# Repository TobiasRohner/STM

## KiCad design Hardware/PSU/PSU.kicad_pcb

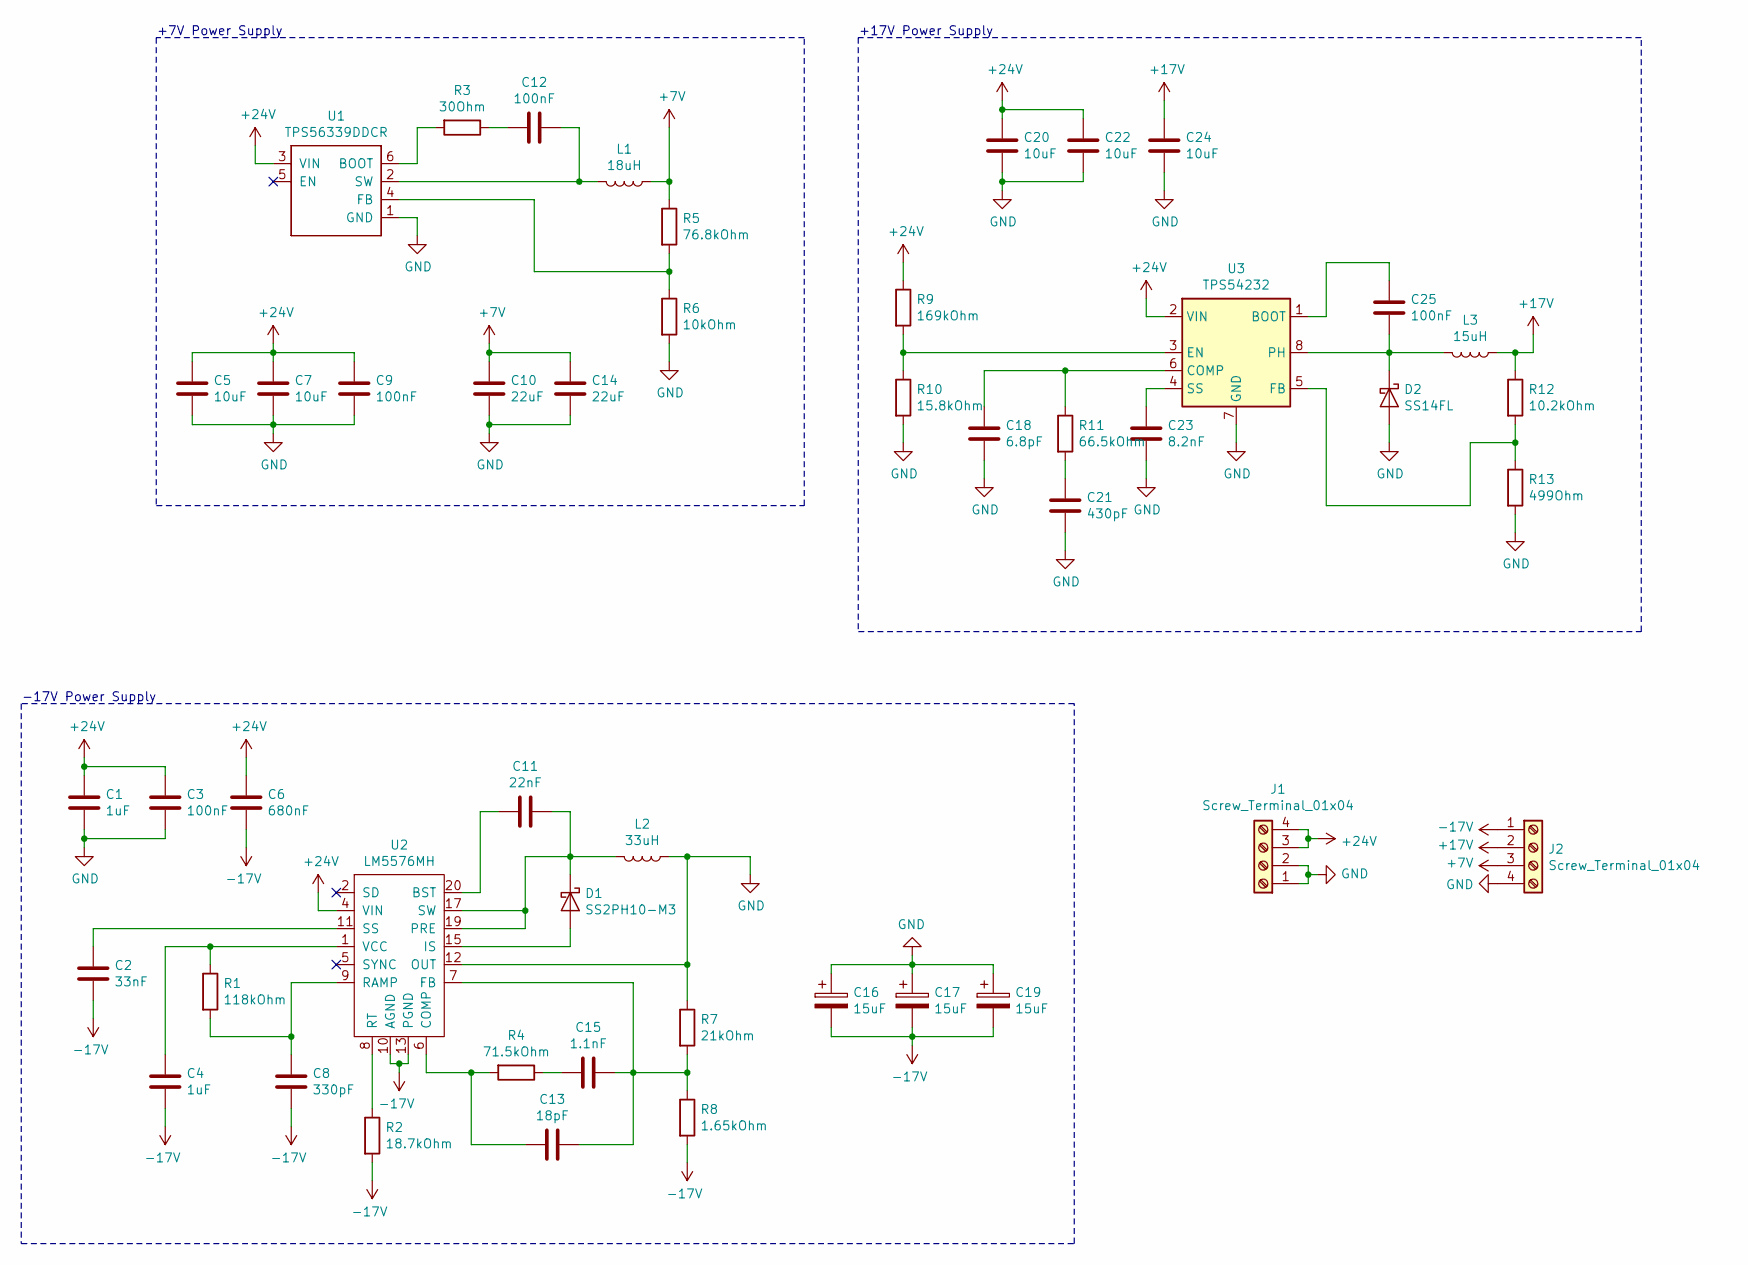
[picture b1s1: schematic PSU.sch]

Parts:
C1, C4: 1uF; C_0603_1608Metric_Pad1.05x0.95mm_HandSolder
C2: 33nF; C_0603_1608Metric_Pad1.05x0.95mm_HandSolder
C3, C9, C12: 100nF; C_0805_2012Metric_Pad1.15x1.40mm_HandSolder
C5, C7: 10uF; C_0805_2012Metric_Pad1.15x1.40mm_HandSolder
C6: 680nF; C_0805_2012Metric_Pad1.15x1.40mm_HandSolder
C8: 330pF; C_0603_1608Metric_Pad1.05x0.95mm_HandSolder
C10, C14: 22uF; C_1210_3225Metric_Pad1.42x2.65mm_HandSolder
C11: 22nF; C_0603_1608Metric_Pad1.05x0.95mm_HandSolder
C13: 18pF; C_0603_1608Metric_Pad1.05x0.95mm_HandSolder
C15: 1.1nF; C_0603_1608Metric_Pad1.05x0.95mm_HandSolder
C16, C17, C19: 15uF; CP_EIA-3528-21_Kemet-B_Pad1.50x2.35mm_HandSolder
C18: 6.8pF; C_0603_1608Metric_Pad1.05x0.95mm_HandSolder
C20, C22, C24: 10uF; C_1206_3216Metric_Pad1.42x1.75mm_HandSolder
C21: 430pF; C_0603_1608Metric_Pad1.05x0.95mm_HandSolder
C23: 8.2nF; C_0201_0603Metric
C25: 100nF; C_0603_1608Metric_Pad1.05x0.95mm_HandSolder
D1: SS2PH10-M3; DO-220AA
D2: SS14FL; SMAF
J1, J2: Screw_Terminal_01x04; BarrierBlock
L1: 18uH; MWSA1206S
L2: 33uH; MWSA1206S
L3: 15uH; MSA75-150M
R1: 118kOhm; R_0603_1608Metric_Pad1.05x0.95mm_HandSolder
R2: 18.7kOhm; R_0603_1608Metric_Pad1.05x0.95mm_HandSolder
R3: 30Ohm; R_0603_1608Metric_Pad1.05x0.95mm_HandSolder
R4: 71.5kOhm; R_0603_1608Metric_Pad1.05x0.95mm_HandSolder
R5: 76.8kOhm; R_0603_1608Metric_Pad1.05x0.95mm_HandSolder
R6: 10kOhm; R_0603_1608Metric_Pad1.05x0.95mm_HandSolder
R7: 21kOhm; R_0603_1608Metric_Pad1.05x0.95mm_HandSolder
R8: 1.65kOhm; R_0603_1608Metric_Pad1.05x0.95mm_HandSolder
R9: 169kOhm; R_0603_1608Metric_Pad1.05x0.95mm_HandSolder
R10: 15.8kOhm; R_0603_1608Metric_Pad1.05x0.95mm_HandSolder
R11: 66.5kOhm; R_0603_1608Metric_Pad1.05x0.95mm_HandSolder
R12: 10.2kOhm; R_0603_1608Metric_Pad1.05x0.95mm_HandSolder
R13: 499Ohm; R_0603_1608Metric_Pad1.05x0.95mm_HandSolder
U1: TPS56339DDCR; TSOT-23-6_HandSoldering
U2: LM5576MH; HTSSOP-20-1EP_4.4x6.5mm_P0.65mm_EP3.4x6.5mm_Mask2.75x3.43mm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
U3: TPS54232; SOIC-8_3.9x4.9mm_P1.27mm

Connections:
+7V: C10.1, C14.1, J2.3, L1.1, R5.1
+17V: C24.1, J2.2, L3.1, R12.1
+24V: C1.1, C3.1, C5.1, C6.1, C7.1, C9.1, C20.1, C22.1, J1.3, J1.4, R9.1, U1.3 (VIN), U2.3 (VIN), U2.4 (VIN), U3.2 (VIN)
-17V: C2.2, C4.2, C6.2, C8.2, C16.2, C17.2, C19.2, J2.1, R2.2, R8.2, U2.10 (AGND), U2.13 (PGND), U2.14 (PGND), U2.21 (AGND)
GND: C1.2, C3.2, C5.2, C7.2, C9.2, C10.2, C14.2, C16.1, C17.1, C18.2, C19.1, C20.2, C21.2, C22.2, C23.2, C24.2, D2.2 (A), J1.1, J1.2, J2.4, L2.1, R6.2, R7.1, R10.2, R13.2, U1.1 (GND), U2.12 (OUT), U3.7 (GND)
unnamed: C2.1, U2.11 (SS)
unnamed: C4.1, R1.1, U2.1 (VCC)
unnamed: C8.1, R1.2, U2.9 (RAMP)
unnamed: C11.1, D1.1 (K), L2.2, U2.17 (SW), U2.18 (SW), U2.19 (PRE)
unnamed: C11.2, U2.20 (BST)
unnamed: C12.1, L1.2, U1.2 (SW)
unnamed: C12.2, R3.1
unnamed: C13.1, C15.1, R7.2, R8.1, U2.7 (FB)
unnamed: C13.2, R4.2, U2.6 (COMP)
unnamed: C15.2, R4.1
unnamed: C18.1, R11.1, U3.6 (COMP)
unnamed: C21.1, R11.2
unnamed: C23.1, U3.4 (SS)
unnamed: C25.1, U3.1 (BOOT)
unnamed: C25.2, D2.1 (K), L3.2, U3.8 (PH)
unnamed: D1.2 (A), U2.15 (IS), U2.16 (IS)
unnamed: R2.1, U2.8 (RT)
unnamed: R3.2, U1.6 (BOOT)
unnamed: R5.2, R6.1, U1.4 (FB)
unnamed: R9.2, R10.1, U3.3 (EN)
unnamed: R12.2, R13.1, U3.5 (FB)

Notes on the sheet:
+7V Power Supply
+17V Power Supply
-17V Power Supply

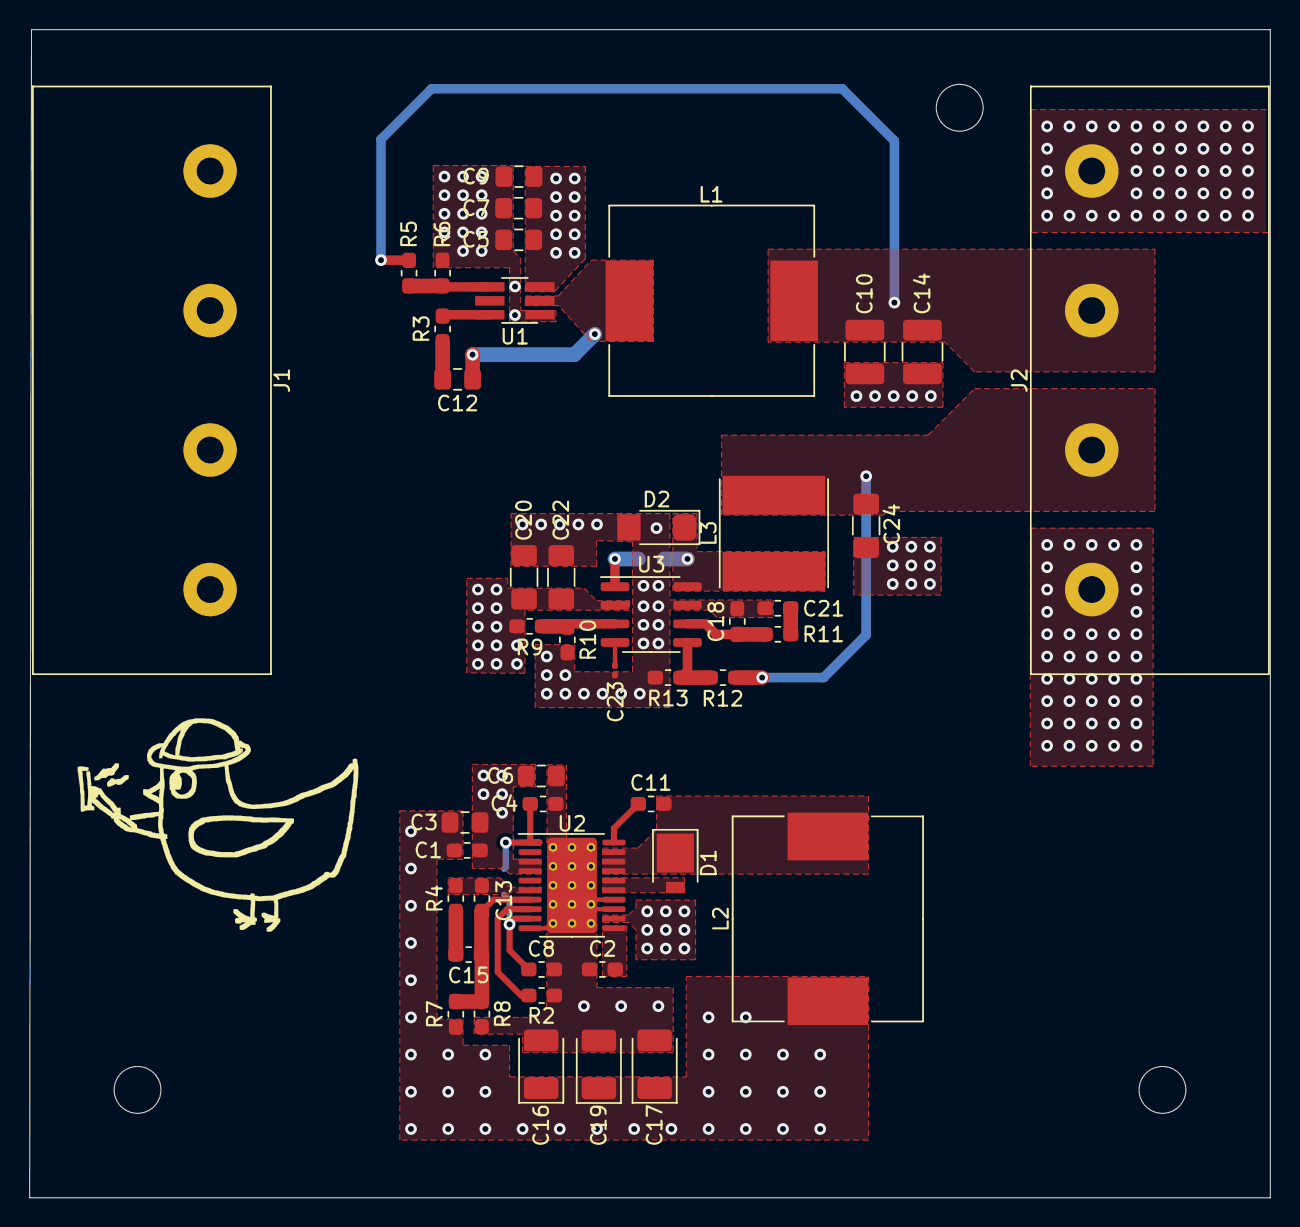
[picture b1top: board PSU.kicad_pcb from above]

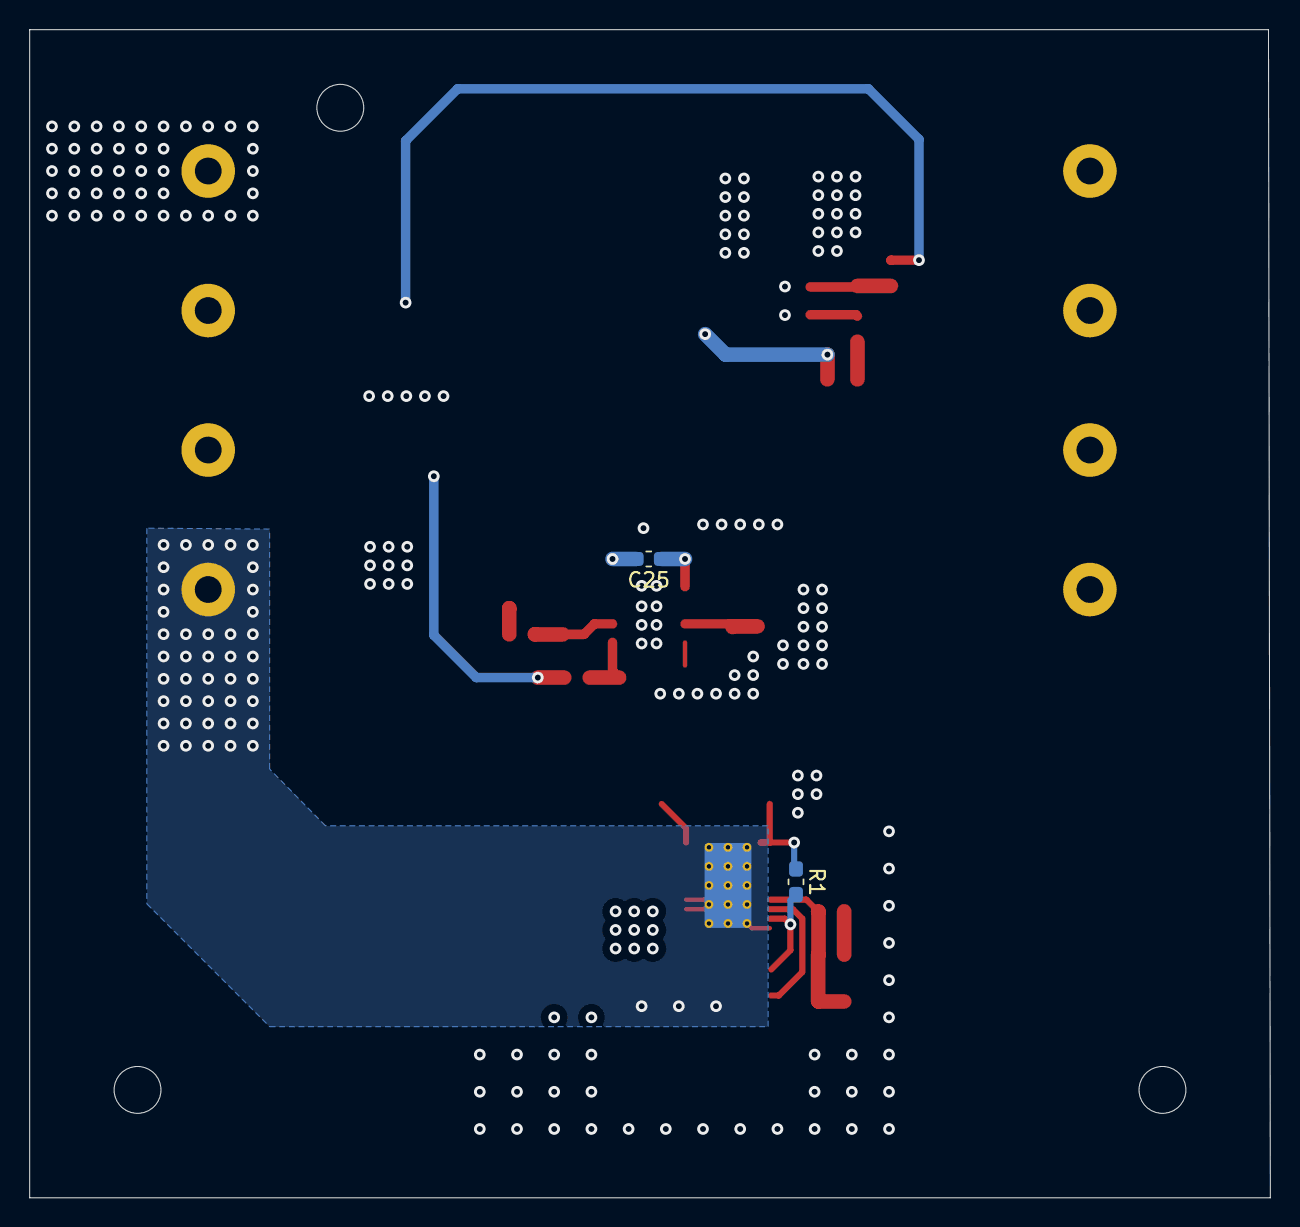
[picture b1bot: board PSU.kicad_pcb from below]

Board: 4 copper layers, 84.7 x 79.8 mm, 48 parts (2 on the bottom side), 26 nets.

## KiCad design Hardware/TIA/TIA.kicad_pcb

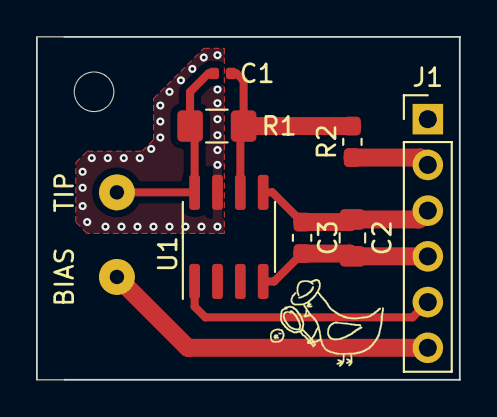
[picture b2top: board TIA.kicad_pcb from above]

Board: 2 copper layers, 23.5 x 19.1 mm, 9 parts (0 on the bottom side), 7 nets.

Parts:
C1: 300fF; C_0402_1005Metric
C2: 4.7uF; C_0805_2012Metric_Pad1.15x1.40mm_HandSolder
C3: 100nF; C_0603_1608Metric_Pad1.05x0.95mm_HandSolder
J1: Conn_01x06_Male; PinHeader_1x06_P2.54mm_Vertical
J2: TIP; SolderWirePad_1x01_Drill0.8mm
J3: BIAS; SolderWirePad_1x01_Drill0.8mm
R1: 100MOhm; R_1206_3216Metric_Pad1.42x1.75mm_HandSolder
R2: 750Ohm; R_0603_1608Metric_Pad1.05x0.95mm_HandSolder
U1: ADA4530-1; SOIC-8_3.9x4.9mm_P1.27mm

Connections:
+15V: C2.1, C3.1, J1.3, U1.5
BIAS: J1.6, J3.1
GND: C2.2, C3.2, J1.1, J1.4, U1.4
unnamed: C1.1, R1.1, R2.2, U1.6
unnamed: C1.2, J2.1, R1.2, U1.8
TIA_DATA: J1.2, R2.1
V_TIP: J1.5, U1.1

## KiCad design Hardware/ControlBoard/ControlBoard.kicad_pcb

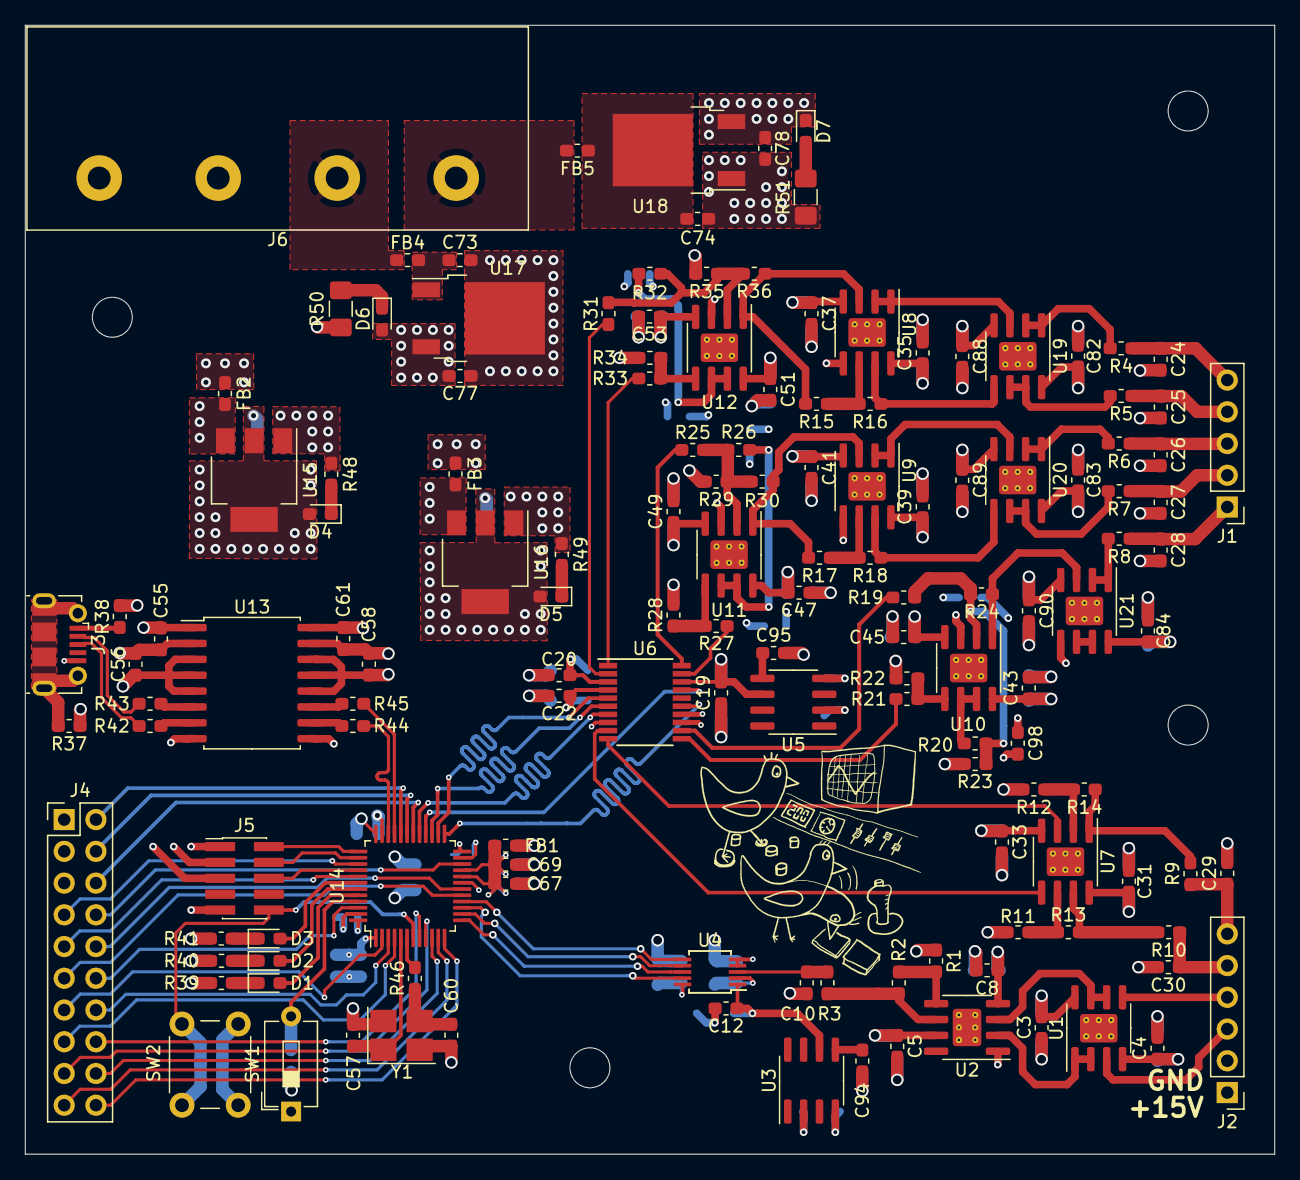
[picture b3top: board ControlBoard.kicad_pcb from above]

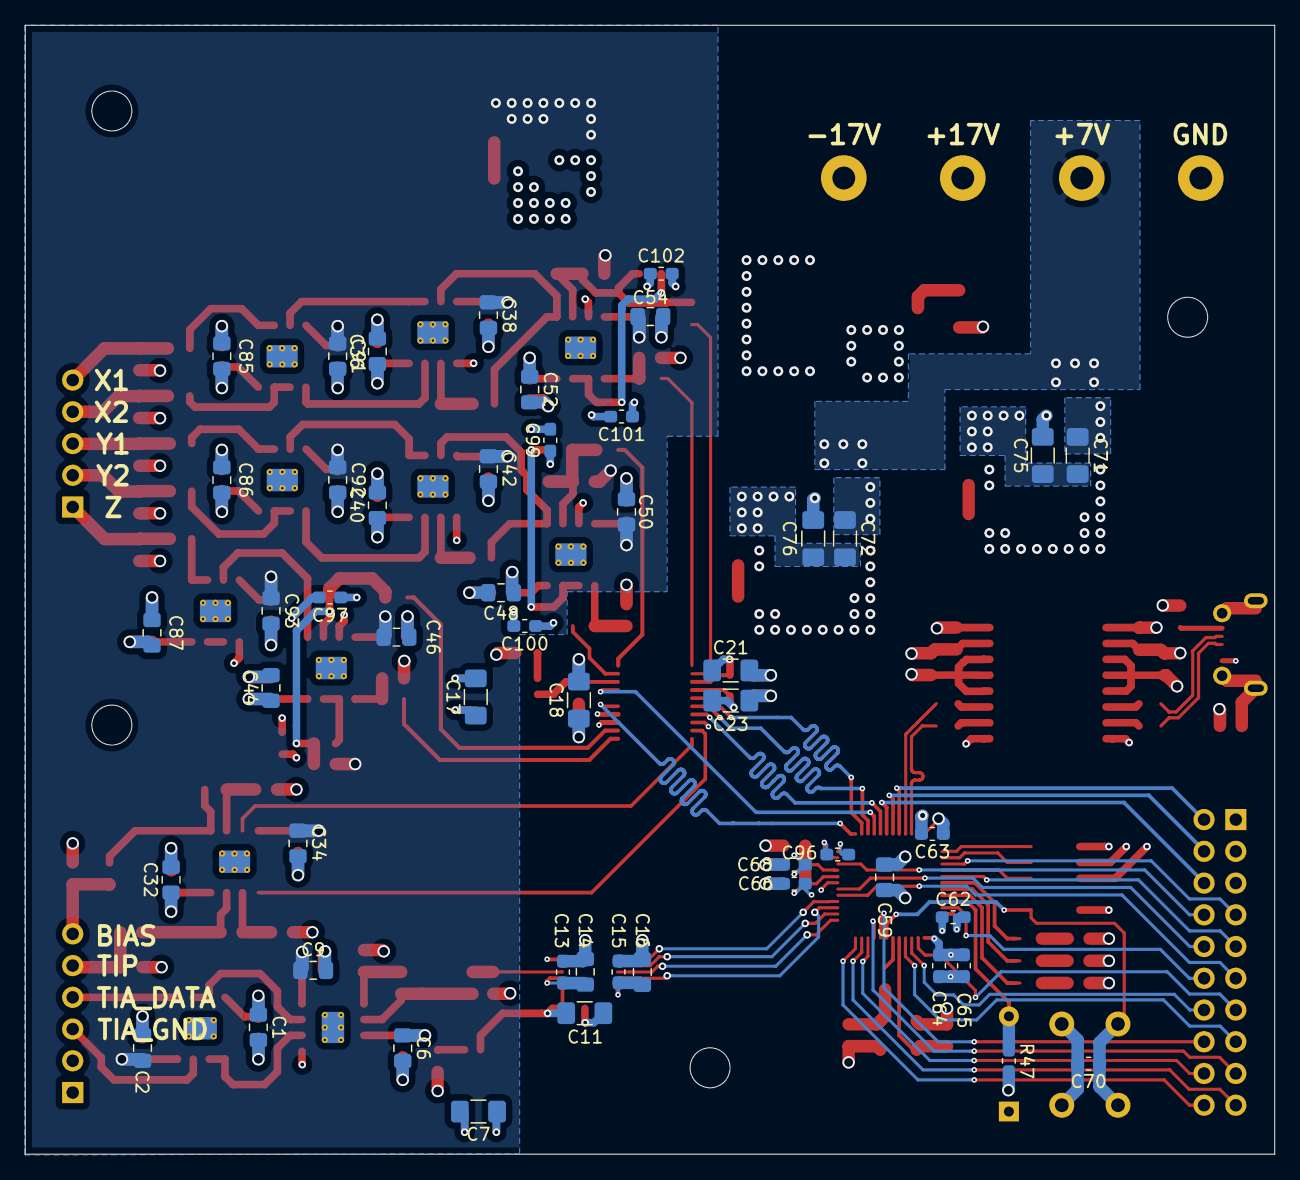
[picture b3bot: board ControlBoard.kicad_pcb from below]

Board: 4 copper layers, 100.0 x 90.4 mm, 192 parts (51 on the bottom side), 123 nets.

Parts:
C1, C2, C6, C9, C14, C16, C32, C34, C36, C38, C40, C42, C44, C46, C48, C50, C52, C54, C59, C85, C86, C87, C91, C92, C93: 4.7uF; C_0805_2012Metric_Pad1.15x1.40mm_HandSolder
C3, C4, C5, C8, C13, C15, C20, C22, C31, C33, C35, C37, C39, C41, C43, C45, C47, C49, C51, C53, C55, C56, C58, C61, C62, C63, C65, C69, C70, C82, C83, C84, C88, C89, C90, C96, C97, C98, C99, C100, C101, C102: 100nF; C_0603_1608Metric_Pad1.05x0.95mm_HandSolder
C7, C17, C21, C23, C71, C72, C75, C76: 10uF; C_1206_3216Metric_Pad1.42x1.75mm_HandSolder
C10: 2.7nF; C_0603_1608Metric_Pad1.05x0.95mm_HandSolder
C11, C18: 47uF; C_1206_3216Metric_Pad1.42x1.75mm_HandSolder
C12, C19, C64, C66, C68, C77, C78, C94, C95: 1uF; C_0603_1608Metric_Pad1.05x0.95mm_HandSolder
C24, C25, C26, C27, C28, C29, C30: 820pF; C_0603_1608Metric_Pad1.05x0.95mm_HandSolder
C57, C60: 12pF; C_0603_1608Metric_Pad1.05x0.95mm_HandSolder
C67: 10nF; C_0603_1608Metric_Pad1.05x0.95mm_HandSolder
C73, C74: 330nF; C_0603_1608Metric_Pad1.05x0.95mm_HandSolder
D1: LED_R; LED_0603_1608Metric_Pad1.05x0.95mm_HandSolder
D2: LED_Y; LED_0603_1608Metric_Pad1.05x0.95mm_HandSolder
D3: LED_G; LED_0603_1608Metric_Pad1.05x0.95mm_HandSolder
D4, D5, D6, D7: LED; LED_0603_1608Metric_Pad1.05x0.95mm_HandSolder
FB1, FB2, FB3, FB4, FB5: 100 @ 100MHz; L_0603_1608Metric_Pad1.05x0.95mm_HandSolder
J1: Piezo; PinHeader_1x05_P2.54mm_Vertical
J2: TIA; PinHeader_1x06_P2.54mm_Vertical
J3: USB_B_Micro; USB_Micro-B_Molex-105017-0001
J4: Conn_02x10_Odd_Even; PinHeader_2x10_P2.54mm_Vertical
J5: Conn_02x05_Odd_Even; PinHeader_2x05_P1.27mm_Vertical_SMD
J6: Screw_Terminal_01x04; BarrierBlock
R1, R15, R16, R17, R18, R47: 10kOhm; R_0603_1608Metric_Pad1.05x0.95mm_HandSolder
R2: 27kOhm; R_0603_1608Metric_Pad1.05x0.95mm_HandSolder
R3: 330Ohm; R_0603_1608Metric_Pad1.05x0.95mm_HandSolder
R4, R5, R6, R7, R8, R9, R10: 750Ohm; R_0603_1608Metric_Pad1.05x0.95mm_HandSolder
R11, R12: 12kOhm; R_0603_1608Metric_Pad1.05x0.95mm_HandSolder
R13, R14, R20, R24, R26, R30, R32, R36: 20kOhm; R_0603_1608Metric_Pad1.05x0.95mm_HandSolder
R19, R25, R31: 3.9kOhm; R_0603_1608Metric_Pad1.05x0.95mm_HandSolder
R21, R27, R33: 60.4kOm; R_0603_1608Metric_Pad1.05x0.95mm_HandSolder
R22, R28, R34: 232Ohm; R_0603_1608Metric_Pad1.05x0.95mm_HandSolder
R23, R29, R35: 23.2kOhm; R_0603_1608Metric_Pad1.05x0.95mm_HandSolder
R37: 0Ohm; R_0603_1608Metric_Pad1.05x0.95mm_HandSolder
R38: 10Ohm; R_0603_1608Metric_Pad1.05x0.95mm_HandSolder
R39, R40, R41, R48: 1.8kOhm; R_0603_1608Metric_Pad1.05x0.95mm_HandSolder
R42, R43, R44, R45: 24Ohm1%; R_0603_1608Metric_Pad1.05x0.95mm_HandSolder
R46: 220Ohm; R_0603_1608Metric_Pad1.05x0.95mm_HandSolder
R49: 3.3kOhm; R_0603_1608Metric_Pad1.05x0.95mm_HandSolder
R50, R51: 20kOhm; R_1206_3216Metric_Pad1.42x1.75mm_HandSolder
SW1: LCSC#C54957; SW_DIP_SPSTx01_Slide_6.7x4.1mm_W7.62mm_P2.54mm_LowProfile
SW2: LCSC#C480285; SW_PUSH_6mm
U1, U7, U8, U9, U10, U11, U12, U19, U20, U21: OPA2227UA_2K5; SOIC-8-1EP_3.9x4.9mm_P1.27mm_EP2.29x3mm_ThermalVias
U2: INA146UA_2K5; SOIC-8-1EP_3.9x4.9mm_P1.27mm_EP2.29x3mm_ThermalVias
U3, U5: REF5050AIDR; SOIC-8_3.9x4.9mm_P1.27mm
U4: AD7685BRMZ; MSOP-10_3x3mm_P0.5mm
U6: AD5676ARUZ_REEL7; TSSOP-20_4.4x6.5mm_P0.65mm
U13: ADUM4160; SOIC-16W_7.5x10.3mm_P1.27mm
U14: STM32G431C6T6; LQFP-48_7x7mm_P0.5mm
U15: AMS1117-3.3; SOT-223-3_TabPin2
U16: AMS1117-5.0; SOT-223-3_TabPin2
U17: MC78M15_TO252; TO-252-2
U18: MC79M15_TO252; TO-252-2
Y1: 16MHz; Crystal_SMD_3225-4Pin_3.2x2.5mm_HandSoldering

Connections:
+3.3VA: C66.1, C67.1, C68.1, C69.1, FB1.1, U14.20, U14.21
+3V3: C15.1, C16.1, C22.1, C23.1, C58.1, C59.1, C61.1, C62.1, C63.1, C64.1, C65.1, C75.1, C96.1, D4.2, FB1.2, J4.3, J5.1, SW1.1, U4.10, U6.4, U13.12, U13.13, U13.14, U13.16, U14.1, U14.24, U14.36, U14.48, U15.2
+5VA: C13.1, C14.1, C20.1, C21.1, C76.1, D5.2, U4.2, U6.3, U16.2
+7V: FB2.2, FB3.2, J6.3
+15V: C1.1, C3.1, C5.1, C6.1, C7.1, C17.1, C31.1, C32.1, C35.1, C36.1, C39.1, C40.1, C43.1, C44.1, C47.1, C48.1, C51.1, C52.1, C77.1, C82.1, C83.1, C84.1, C85.1, C86.1, C87.1, C97.1, C98.1, C99.1, C100.1, C101.1, C102.1, D6.2, J2.1, U1.8, U2.7, U3.2, U5.2, U7.8, U8.8, U9.8, U10.8, U11.8, U12.8, U17.3, U19.8, U20.8, U21.8
+17V: FB4.2, J6.2
-15V: C2.1, C4.1, C8.1, C9.1, C33.1, C34.1, C37.1, C38.1, C41.1, C42.1, C45.1, C46.1, C49.1, C50.1, C53.1, C54.1, C78.2, C88.1, C89.1, C90.1, C91.1, C92.1, C93.1, D7.1, R23.2, R29.2, R35.2, U1.4, U2.4, U7.4, U8.4, U9.4, U10.4, U11.4, U12.4, U18.3, U19.4, U20.4, U21.4
-17V: FB5.2, J6.1
/ControlLogic/BIAS: C29.1, J2.6, R9.1
/ControlLogic/ControlLogicMixer/BIAS: U6.10, U7.3
/ControlLogic/ControlLogicMixer/BIAS_OUT: R9.2, R14.1, U7.1
/ControlLogic/ControlLogicMixer/CoarseFineMixer_X/OUT: R15.2, R36.1, U8.3, U12.1
/ControlLogic/ControlLogicMixer/CoarseFineMixer_Y/OUT: R17.2, R30.1, U9.3, U11.1
/ControlLogic/ControlLogicMixer/TIP: U6.9, U7.5
/ControlLogic/ControlLogicMixer/TIP_OUT: R10.2, R13.1, U7.7
/ControlLogic/ControlLogicMixer/X1: R31.2, U6.2
/ControlLogic/ControlLogicMixer/X2: R33.1, U6.1
/ControlLogic/ControlLogicMixer/Y1: R25.2, U6.20
/ControlLogic/ControlLogicMixer/Y2: R27.1, U6.19
/ControlLogic/ControlLogicMixer/Z1: R19.2, U6.12
/ControlLogic/ControlLogicMixer/Z2: R21.1, U6.11
/ControlLogic/OutputBuffer/X1_IN: U8.1, U8.2, U19.3
/ControlLogic/OutputBuffer/X1_OUT: R4.2, U19.1, U19.2
/ControlLogic/OutputBuffer/X2_IN: R16.1, U8.7, U19.5
/ControlLogic/OutputBuffer/X2_OUT: R5.2, U19.6, U19.7
/ControlLogic/OutputBuffer/Y1_IN: U9.1, U9.2, U20.3
/ControlLogic/OutputBuffer/Y1_OUT: R6.2, U20.1, U20.2
/ControlLogic/OutputBuffer/Y2_IN: R18.1, U9.7, U20.5
/ControlLogic/OutputBuffer/Y2_OUT: R7.2, U20.6, U20.7
/ControlLogic/OutputBuffer/Z_IN: R24.1, U10.1, U21.3
/ControlLogic/OutputBuffer/Z_OUT: R8.2, U21.1, U21.2
/ControlLogic/TIP: C30.1, J2.5, R10.1
/ControlLogic/X1: C24.1, J1.5, R4.1
/ControlLogic/X2: C25.1, J1.4, R5.1
/ControlLogic/Y1: C26.1, J1.3, R6.1
/ControlLogic/Y2: C27.1, J1.2, R7.1
/ControlLogic/Z: C28.1, J1.1, R8.1
/DataAquisition/TIA_DATA: J2.4, U1.5
/DataAquisition/TIA_GND: J2.3, U1.3
BOOT0: R47.1, SW1.2, U14.45
DA_CNV: U4.6, U14.16
GND: C1.2, C2.2, C3.2, C4.2, C5.2, C6.2, C7.2, C8.2, C9.2, C10.2, C11.1, C12.1, C13.2, C14.2, C15.2, C16.2, C17.2, C18.1, C19.1, C20.2, C21.2, C22.2, C23.2, C24.2, C25.2, C26.2, C27.2, C28.2, C29.2, C30.2, C31.2, C32.2, C33.2, C34.2, C35.2, C36.2, C37.2, C38.2, C39.2, C40.2, C41.2, C42.2, C43.2, C44.2, C45.2, C46.2, C47.2, C48.2, C49.2, C50.2, C51.2, C52.2, C53.2, C54.2, C57.2, C58.2, C59.2, C60.2, C61.2, C62.2, C63.2, C64.2, C65.2, C66.2, C67.2, C68.2, C69.2, C70.2, C71.2, C72.2, C73.2, C74.1, C75.2, C76.2, C77.2, C78.1, C82.2, C83.2, C84.2, C85.2, C86.2, C87.2, C88.2, C89.2, C90.2, C91.2, C92.2, C93.2, C94.2, C95.2, C96.2, C97.2, C98.2, C99.2, C100.2, C101.2, C102.2, J2.2, J4.1, J4.5, J5.3, J5.5, J5.9, J6.4, R1.1, R11.2, R12.2, R22.2, R28.2, R34.2, R39.1, R40.1, R41.1, R47.2, R48.2, R49.2, R50.2, R51.1, SW2.2, U2.1, U3.4, U4.4, U4.5, U5.4, U6.8, U6.13, U6.14, U8.5, U9.5, U10.3, U11.3, U12.3, U13.9, U13.15, U14.19, U14.23, U14.35, U14.47, U15.1, U16.1, U17.2, U18.1, U21.5, Y1.2, Y1.4
GNDUSB: C55.2, C56.2, J3.5, R37.1, U13.2, U13.8
LED_G: D3.2, U14.42
LED_R: D1.2, U14.44
LED_Y: D2.2, U14.43
NRST: C70.1, J5.10, SW2.1, U14.7
unnamed: C10.1, R3.1, U4.3
unnamed: C11.2, C12.2, U3.6, U4.1
unnamed: C18.2, C19.2, U5.6, U6.18
unnamed: C57.1, U14.5, Y1.1
unnamed: C60.1, R46.2, Y1.3
unnamed: C71.1, FB2.1, U15.3
unnamed: C72.1, FB3.1, U16.3
unnamed: C73.1, FB4.1, U17.1
unnamed: C74.2, FB5.1, U18.2
unnamed: C94.1, U3.5
unnamed: C95.1, U5.5
unnamed: D1.1, R39.2
unnamed: D2.1, R40.2
unnamed: D3.1, R41.2
unnamed: D4.1, R48.1
unnamed: D5.1, R49.1
unnamed: D6.1, R50.1
unnamed: D7.2, R51.2
unnamed: J3.1, R38.2
unnamed: J3.6, R37.2
unnamed: R1.2, R2.1, U2.5
unnamed: R2.2, R3.2, U2.6
unnamed: R11.1, R13.2, U7.6
unnamed: R12.1, R14.2, U7.2
unnamed: R15.1, R16.2, U8.6
unnamed: R17.1, R18.2, U9.6
unnamed: R19.1, R20.1, R23.1, R24.2, U10.2
unnamed: R20.2, U10.6, U10.7
unnamed: R21.2, R22.1, U10.5
unnamed: R25.1, R26.1, R29.1, R30.2, U11.2
unnamed: R26.2, U11.6, U11.7
unnamed: R27.2, R28.1, U11.5
unnamed: R31.1, R32.1, R35.1, R36.2, U12.2
unnamed: R32.2, U12.6, U12.7
unnamed: R33.2, R34.1, U12.5
unnamed: R42.1, U13.7
unnamed: R43.1, U13.6
unnamed: R44.2, U13.10
unnamed: R45.1, U13.11
unnamed: R46.1, U14.6
unnamed: U1.1, U1.2, U2.2
unnamed: U1.6, U1.7, U2.3
unnamed: U21.6, U21.7
PA0: J4.16, U14.8
PA1: J4.17, U14.9
PA2: J4.18, U14.10
PA3: J4.19, U14.11
PA4: J4.20, U14.12
PA8: J4.6, U14.30
PA15: J4.7, U14.39
PB1: J4.11, U14.17
PB2: J4.10, U14.18
PB4: J4.9, U14.41
PB9: J4.12, U14.46
PB10: J4.8, U14.22
PC13: J4.13, U14.2
PC14: J4.14, U14.3
PC15: J4.15, U14.4
SPI1_MISO: U4.7, U14.14
SPI1_MOSI: U4.9, U14.15
SPI1_SCK: U4.8, U14.13
SPI2_MOSI: U6.7, U14.29
SPI2_SCK: U6.6, U14.27
SWCLK: J5.4, U14.38
SWDIO: J5.2, U14.37
SWO: J5.6, U14.40
UD+: J3.3, R42.2
UD-: J3.2, R43.2
USART1_RX: J4.2, U14.32
USART1_TX: J4.4, U14.31
USB_D+: R44.1, U14.34
USB_D-: R45.2, U14.33
VBUS: C55.1, C56.1, R38.1, U13.1, U13.3, U13.4, U13.5
~CTRL_LDAC: U6.15, U14.25
~CTRL_RESET: U6.17, U14.28
~CTRL_SYNC: U6.5, U14.26

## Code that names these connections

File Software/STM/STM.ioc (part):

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Mcu.Name=STM32G431C(6-8-B)Tx
Mcu.Package=LQFP48
Mcu.UserName=STM32G431C6Tx
PA10.Mode=Asynchronous
PA10.Signal=USART1_RX
PA11.Mode=Device
PA11.Signal=USB_DM
PA12.Mode=Device
PA12.Signal=USB_DP
PA13.Mode=Trace_Asynchronous_SW
PA13.Signal=SYS_JTMS-SWDIO
PA14.Mode=Trace_Asynchronous_SW
PA14.Signal=SYS_JTCK-SWCLK
PA5.Mode=RX_Only_Simplex_Unidirect_Master
PA5.Signal=SPI1_SCK
PA6.Mode=RX_Only_Simplex_Unidirect_Master
PA6.Signal=SPI1_MISO
PA7.GPIOParameters=GPIO_Label
PA7.GPIO_Label=SPI1_MOSI
PA7.Signal=GPIO_Output
PA9.Mode=Asynchronous
PA9.Signal=USART1_TX
PB0.GPIOParameters=GPIO_Label
PB0.GPIO_Label=DA_CNV
PB0.Signal=GPIO_Output
PB11.GPIOParameters=GPIO_Label
PB11.GPIO_Label=CTRL_LDAC_INV
PB11.Signal=GPIO_Output
PB12.GPIOParameters=GPIO_Label
PB12.GPIO_Label=CTRL_SYNC_INV
PB12.Signal=GPIO_Output
PB13.Mode=TX_Only_Simplex_Unidirect_Master
PB13.Signal=SPI2_SCK
PB14.GPIOParameters=GPIO_Label
PB14.GPIO_Label=CTRL_RESET_INV
PB14.Signal=GPIO_Output
PB15.Mode=TX_Only_Simplex_Unidirect_Master
PB15.Signal=SPI2_MOSI
PB3.Mode=Trace_Asynchronous_SW
PB3.Signal=SYS_JTDO-SWO
PB5.GPIOParameters=GPIO_Label
PB5.GPIO_Label=LED_G
PB5.Signal=GPIO_Output
PB6.GPIOParameters=GPIO_Label
PB6.GPIO_Label=LED_Y
PB6.Signal=GPIO_Output
PB7.GPIOParameters=GPIO_Label
PB7.GPIO_Label=LED_R
PB7.Signal=GPIO_Output
PB8-BOOT0.GPIOParameters=GPIO_Label
PB8-BOOT0.GPIO_Label=BOOT0
PB8-BOOT0.Signal=GPIO_Analog
PF0-OSC_IN.Mode=HSE-External-Oscillator
PF0-OSC_IN.Signal=RCC_OSC_IN
PF1-OSC_OUT.Mode=HSE-External-Oscillator
PF1-OSC_OUT.Signal=RCC_OSC_OUT
PG10-NRST.GPIOParameters=GPIO_Label
PG10-NRST.GPIO_Label=NRST
PG10-NRST.Signal=GPIO_Analog
RCC.HSE_VALUE=16000000
RCC.SYSCLKFreq_VALUE=96000000
RCC.SYSCLKSource=RCC_SYSCLKSOURCE_PLLCLK
board=custom
